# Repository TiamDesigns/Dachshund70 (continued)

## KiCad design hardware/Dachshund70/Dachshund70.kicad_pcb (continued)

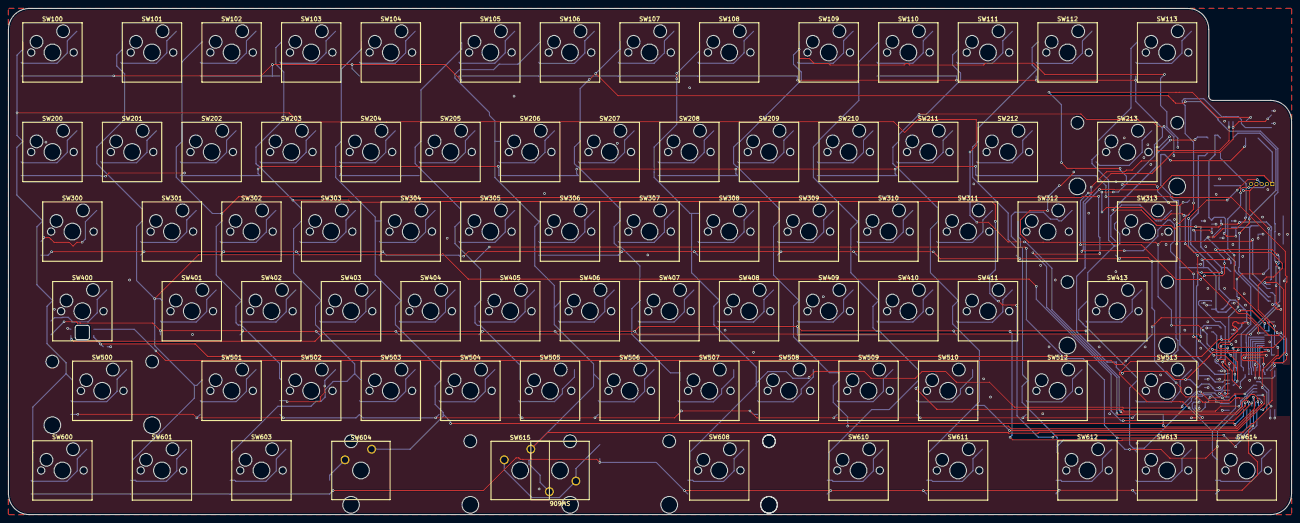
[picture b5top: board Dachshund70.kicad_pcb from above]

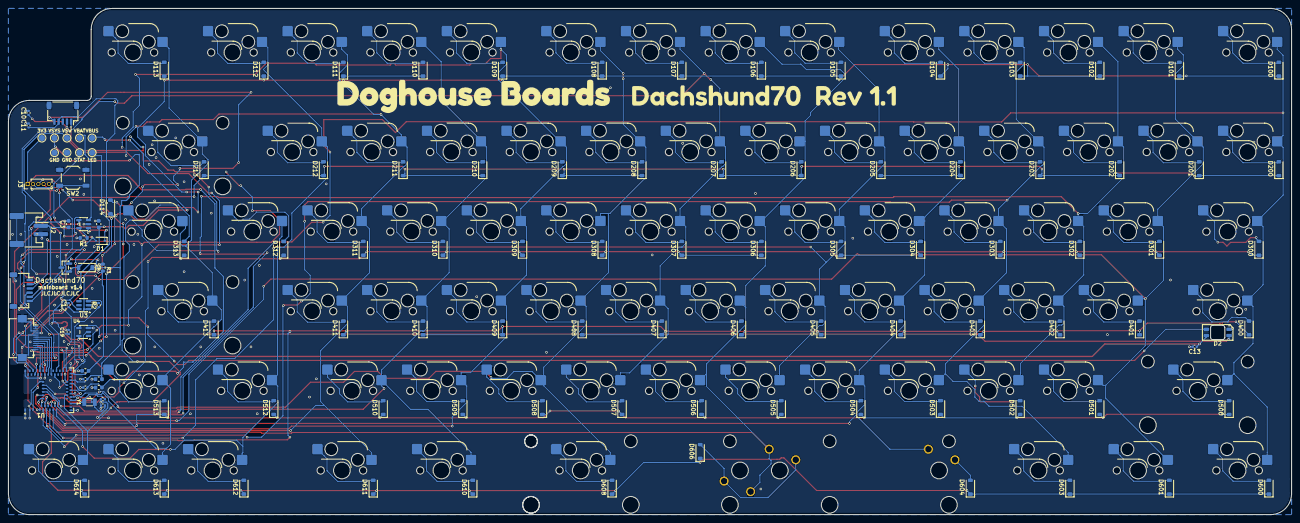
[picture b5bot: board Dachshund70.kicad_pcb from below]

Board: 2 copper layers, 307.0 x 121.1 mm, 207 parts (121 on the bottom side), 130 nets.

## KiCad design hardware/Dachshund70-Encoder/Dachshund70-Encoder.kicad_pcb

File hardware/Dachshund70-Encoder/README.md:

# Dachshund70 encoder module

The roller encoder on its own small board, cabled to the mainboard. Introduced with mainboard Rev 1.1,
which no longer carries the encoder. KiCad 10 project, 2 layers, 1.6 mm FR4.

- **Encoder:** SW1, Bourns PEC12R-2230F-S0024 (shaft parallel to the board, 24 detents, 24 pulses per turn,
  30 mm shaft, push switch pressed along the shaft; no LCSC listing, so source it globally or solder it by hand).
  The 30 mm shaft carries the 2u roller (about 25 mm long, on 19 mm of shaft). Same body and footprint as the
  20 mm PEC12R-2220F-S0024 it replaces (`../3dmodels/Bourns_PEC12R-2x30F-S_standin.step`). Through-hole; its two
  frame tabs are on GND.
- **Cable port:** J1, JST SH 1.0 mm, 5 pins, side entry (SM05B-SRSS-TB), on the **bottom** side, its mouth facing
  +u (toward the shaft). The mainboard's J5 faces it across the notch on the same line, so the cable runs straight
  under the module: about 25 mm overall (housing end to end), 5 parallel wires with both latches on the same side,
  which makes it a reversed cable (J1 pin n to J5 pin 6 − n; the pin numbers below are matched to that). Crimp it
  from SHR-05V-S housings and SSH-003T contacts with 30–32 AWG wire, or shorten a pre-made reversed cable.
  Trim the encoder's through-hole pins to 0.5 mm or less on the bottom: the cable runs right under them (it touches
  the push switch's uncut pins in the model, 0.3 under the A/B/C pins).
- **Nothing else.** The 10 nF debounce capacitors on A and B and the push-switch diode D114 stay on the
  mainboard, so the pin map and the firmware did not change. No expansion ports on either board.

| J5 pin (mainboard) | J1 pin (module) | Net | Encoder pad | MCU pin |
| --- | --- | --- | --- | --- |
| 1 | 5 | COL14 | S1 (push switch) | matrix column 14, with diode D114 on the mainboard |
| 2 | 4 | ENC_A | A | P0.11 |
| 3 | 3 | GND | C (common) | |
| 4 | 2 | ENC_B | B | P0.12 |
| 5 | 1 | ENC_SW | S2 (push switch) | matrix row 0 through D114 |

## Geometry

Module coordinates: u runs along the shaft, toward the hub end of the board (+x of the mainboard's old
encoder); v runs across it (+y); (0, 0) is the board's top-left corner seen from above. Z is measured up
from the PCB's top face.

- Outline 22.5 (u) × 22.0 (v) mm, 1.5 mm corner radius. The right edge is the hub end of the shaft; the wheel
  starts there and the board has nothing under it.
- Encoder pad C at (15.0, 11.0). Body rear face u = 11.5, front face u = 17.5, hub to u = 22.5, shaft tip at
  u = 41.5 (30 mm shaft). Shaft axis at v = 11.0 and 10.0 mm above the PCB top.
- Two mounting holes, 2.2 mm (M2), at (2.7, 2.7) and (2.7, 19.3). The 12.5 mm-wide encoder body spans
  v 4.75 to 17.25.
- J1's pad row at u = 1.3, v = 9 (pin 1) to 13 (pin 5); its body is u 0.8 to 5.8 and its mouth faces +u, so the
  plug sits under the module's left half and the cable leaves toward +u, under the encoder (mainboard x 309.7).
  (Before round 5 it faced -u, into the mainboard's notch edge, where no plug could go in.)
- On the mainboard, J5 is on the back to the right of the corner notch: footprint at (329.8, 49.54) rot 90, pad
  row at x = 331.8 mm, y = 47.54 (pin 5) to 51.54 (pin 1), on the same line as J1 (centre y 49.54, the shaft's
  axis), mouth at x 327.3 facing -x into the notch. The two mouths are 17.6 mm apart; the cable drops 1.8 mm from
  J1 (under the module, z 1.8) to J5 (under the mainboard), and the plate is 7.4 mm above it (6.4 when it floats
  down 1 mm). The notch is open to the mainboard's top edge, x 304.0 to 326.4 mm and y 39.0 to
  57.0 mm, so the module (left edge at x 303.905) sits in it, with a 4.2 mm lobe at (306.6, 57.8) for the
  head of its lower M2 screw (its post is at y 57.82); the upper screw head is inside the notch.

## Status

DRC (kicad-cli, with schematic parity): 0 errors and 0 unconnected items. The only messages are the
library-footprint mismatch on SW1 (the board copy of the footprint is the project's own, like the mainboard's)
and the missing MPN fields that the mainboard also shows. ERC: 0. Not ordered, made or fitted.

LCSC part numbers are blank: the encoder has no LCSC listing (see PROGRESS.md, 2026-10-28), and J1's number
is still to be confirmed, so JLC would source both globally or you solder the encoder by hand.

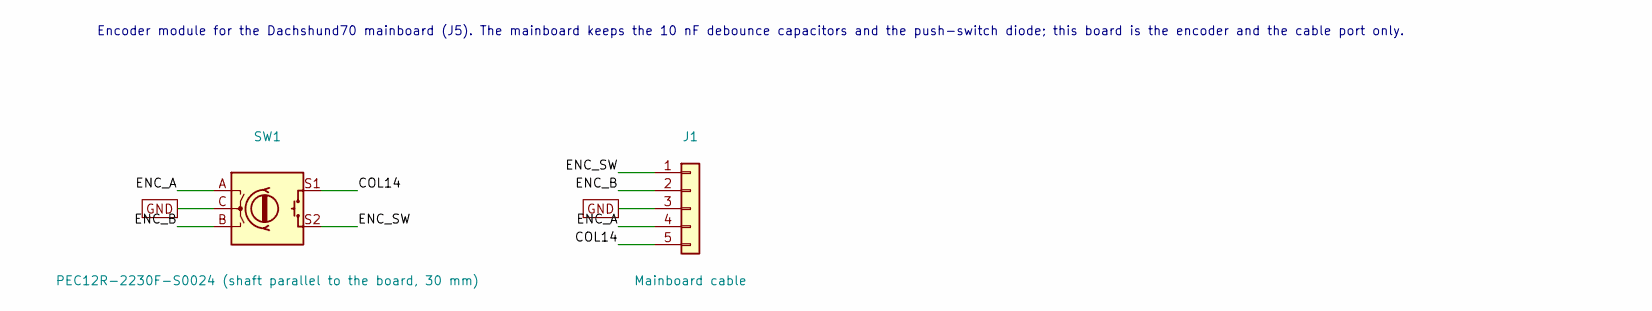
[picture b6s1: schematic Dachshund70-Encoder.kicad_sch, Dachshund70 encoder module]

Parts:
J1: Mainboard cable; JST_SH_SM05B-SRSS-TB_1x05-1MP_P1.00mm_Horizontal; MPN JST SM05B-SRSS-TB
SW1: PEC12R-2230F-S0024 (shaft parallel to the board, 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; RotaryEncoder_Bourns_Horizontal_PEC12R-2x17F-Sxxxx; MPN Bourns PEC12R-2230F-S0024

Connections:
/COL14: J1.5, SW1.S1
/ENC_A: J1.4, SW1.A
/ENC_B: J1.2, SW1.B
/ENC_SW: J1.1, SW1.S2
GND: J1.3, SW1.C

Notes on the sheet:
Encoder module for the Dachshund70 mainboard (J5). The mainboard keeps the 10 nF debounce capacitors and the push-switch diode; this board is the encoder and the cable port only.

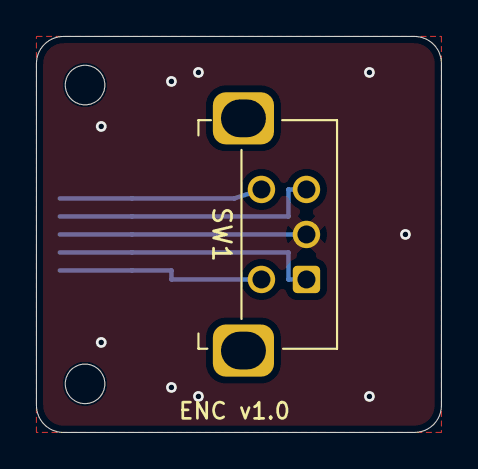
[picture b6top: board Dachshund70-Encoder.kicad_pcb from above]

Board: 2 copper layers, 22.5 x 22.0 mm, 4 parts (1 on the bottom side), 5 nets.

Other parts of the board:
H1, H2: MountingHole_2.2mm_M2

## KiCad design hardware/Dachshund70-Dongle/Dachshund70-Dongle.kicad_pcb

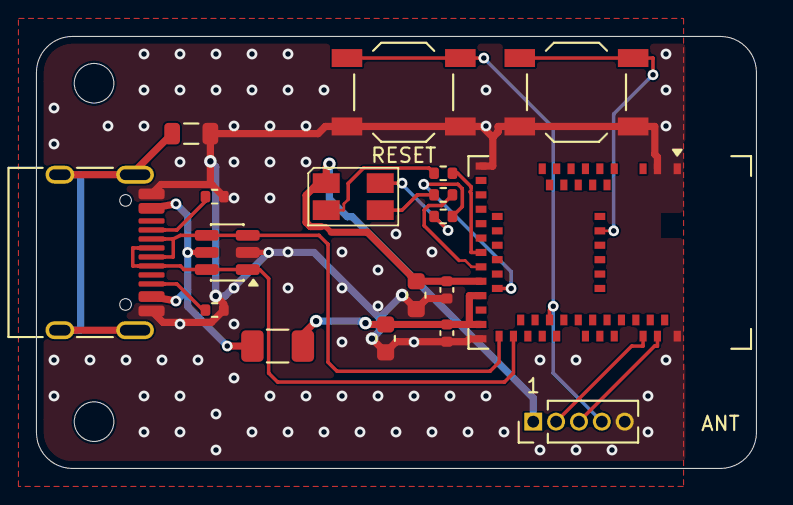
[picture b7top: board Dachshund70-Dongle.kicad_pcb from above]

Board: 2 copper layers, 40.0 x 24.0 mm, 20 parts (0 on the bottom side), 19 nets.

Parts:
C1, C3: 4.7uF; C_0603_1608Metric
C2, C4: 100nF; C_0402_1005Metric
D1: ASMB-MTB0-0A3A2; LED_Avago_PLCC4_3.2x2.8mm_CW
F1: PTC 750mA hold; Fuse_1206_3216Metric
FB1: 600R@100MHz; L_0805_2012Metric
H1, H2: M2; MountingHole_2.2mm_M2
J1: USB-C (HRO TYPE-C-31-M-12); USB_C_Receptacle_HRO_TYPE-C-31-M-12
J2: SWD; PinHeader_1x05_P1.27mm_Vertical
R1, R2: 5.1k; R_0402_1005Metric
R3: 1k; R_0402_1005Metric
R4, R5: 330; R_0402_1005Metric
SW1: Pair; SW_SPST_TL3342
SW2: Reset; SW_SPST_TL3342
U1: USBLC6-2SC6; SOT-23-6
U2: MDBT50Q-P1MV2; Raytac_MDBT50Q

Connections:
/+3V3: C3.1, C4.1, D1.1, J2.1, U2.28
/CC1: J1.A5, R1.1
/CC2: J1.B5, R2.1
/D+: J1.A6, J1.B6, U1.1, U1.6, U2.35
/D-: J1.A7, J1.B7, U1.3, U1.4, U2.34
/LED_B: R5.2, U2.29
/LED_BK: D1.2, R5.1
/LED_G: R4.2, U2.26
/LED_GK: D1.3, R4.1
/LED_R: R3.2, U2.24
/LED_RK: D1.4, R3.1
/NRESET: J2.4, SW2.1, U2.40
/PAIR: SW1.1, U2.57
/SHIELD: FB1.1, J1.SH
/SWDCLK: J2.3, U2.53
/SWDIO: J2.2, U2.51
/VBUS: C1.1, C2.1, F1.2, U2.30, U2.32
/VBUS_RAW: F1.1, J1.A4, J1.A9, J1.B4, J1.B9, U1.5
GND: C1.2, C2.2, C3.2, C4.2, FB1.2, J1.A1, J1.A12, J1.B1, J1.B12, J2.5, R1.2, R2.2, SW1.2, SW2.2, U1.2, U2.1, U2.2, U2.15, U2.33, U2.55

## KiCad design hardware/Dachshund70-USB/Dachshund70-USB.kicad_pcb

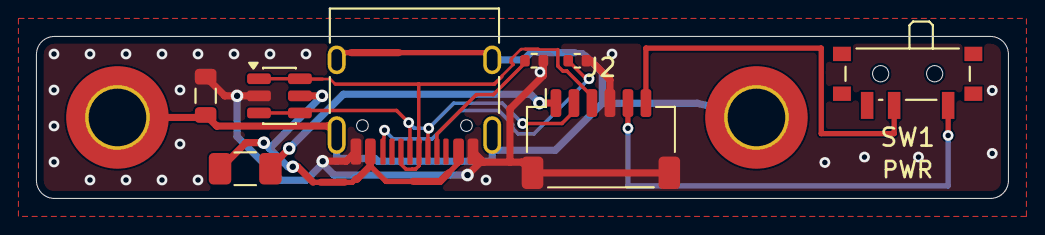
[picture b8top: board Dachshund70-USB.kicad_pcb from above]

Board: 2 copper layers, 54.0 x 9.0 mm, 10 parts (0 on the bottom side), 10 nets.

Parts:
F1: PTC 750mA hold; Fuse_1206_3216Metric
FB1: 600R@100MHz; L_0805_2012Metric
H1, H2: M3; MountingHole_3.2mm_M3_ISO7380_Pad_TopBottom
J1: USB-C (HRO TYPE-C-31-M-12); USB_C_Receptacle_HRO_TYPE-C-31-M-12
J2: Mainboard (JST-SH 6P); JST_SH_SM06B-SRSS-TB_1x06-1MP_P1.00mm_Horizontal
R1, R2: 5.1k; R_0402_1005Metric
SW1: Power; SW_SPDT_PCM12
U1: USBLC6-2SC6; SOT-23-6

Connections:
/CC1: J1.A5, R1.1
/CC2: J1.B5, R2.1
/D+: J1.A6, J1.B6, J2.3, U1.1, U1.6
/D-: J1.A7, J1.B7, J2.2, U1.3, U1.4
/SHIELD: FB1.1, H1.1, H2.1, J1.SH
/VBAT: J2.5, SW1.1
/VBAT_SW: J2.6, SW1.2
/VBUS: F1.2, J2.1
/VBUS_RAW: F1.1, J1.A4, J1.A9, J1.B4, J1.B9, U1.5
GND: FB1.2, J1.A1, J1.A12, J1.B1, J1.B12, J2.4, J2.MP, R1.2, R2.2, U1.2

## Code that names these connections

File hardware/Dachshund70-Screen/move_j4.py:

"""One-off edit of the mainboard: J4, the hand-wired 2.54 mm display header, becomes an
8-pin 0.5 mm FFC socket for the screen board (Hirose FH12-8S, top side, under the plate notch) and the
eight display nets are rerouted to it. Kept for the record; run it once, in KiCad 10's Python, from the
repo root. The schematic side is done separately (J4's symbol becomes Conn_01x08_MountingPin, MP to GND).

J4's pins sit at the same x and y as the screen board's J2 (the FFC loops round between them), so pin n
here meets J2 pin 9 - n. Pin 1 (3V3) is at the back (smaller y), pin 8 (BUSY) at the front. The
socket sits under the plate's screen notch, 2.7 mm behind the SWD header J3 so its body clears J3.
"""
import pcbnew

PCB = "hardware/Dachshund70/Dachshund70.kicad_pcb"
FP_DIR = "/usr/share/kicad/footprints/Connector_FFC-FPC.pretty"
FP_NAME = "Hirose_FH12-8S-0.5SH_1x08-1MP_P0.50mm_Horizontal"
XY = (327.9, 94.9)           # pads y 93.15-96.65, clear of J3 (the SWD header, from y 100.4)
M, F = pcbnew.ToMM, pcbnew.FromMM

b = pcbnew.LoadBoard(PCB)
nets = {n: b.FindNet(n) for n in ("+3V3", "GND", "/DISP_DIN", "/DISP_CLK", "/DISP_CS", "/DISP_DC", "/DISP_RST",
                                  "/DISP_BUSY")}
DISP = [n for n in nets if n.startswith("/DISP")]


TRACKS = list(b.GetTracks())    # looked up once: pcbnew's track list can't be re-read after a Remove
REMOVE = []


def P(x, y):
    return pcbnew.VECTOR2I(F(x), F(y))


def near(a, xy, tol=0.002):
    return abs(M(a.x) - xy[0]) < tol and abs(M(a.y) - xy[1]) < tol


def find_track(net, layer, a, c):
    for t in TRACKS:
        if t in REMOVE:
            continue
        if t.GetClass() == "PCB_VIA" or t.GetNetname() != net or t.GetLayerName() != layer:
            continue
        if (near(t.GetStart(), a) and near(t.GetEnd(), c)) or (near(t.GetStart(), c) and near(t.GetEnd(), a)):
            return t
    raise SystemExit("no track %s %s %r %r" % (net, layer, a, c))


def find_via(net, xy):
    for t in TRACKS:
        if t.GetClass() == "PCB_VIA" and t.GetNetname() == net and near(t.GetPosition(), xy, 0.01):
            return t
    raise SystemExit("no via %s %r" % (net, xy))


def drop_track(net, layer, a, c):
    REMOVE.append(find_track(net, layer, a, c))


def move_end(net, layer, a, c, old, new):
    """Move the end of track a-c that sits at old to new."""
    t = find_track(net, layer, a, c)
    if near(t.GetStart(), old):
        t.SetStart(P(*new))
    else:
        t.SetEnd(P(*new))


def track(net, layer, pts, w):
    for (ax, ay), (cx, cy) in zip(pts, pts[1:]):
        t = pcbnew.PCB_TRACK(b)
        t.SetStart(P(ax, ay))
        t.SetEnd(P(cx, cy))
        t.SetWidth(F(w))
        t.SetLayer(pcbnew.F_Cu if layer == "F" else pcbnew.B_Cu)
        t.SetNet(nets[net])
        b.Add(t)


def via(net, x, y):
    v = pcbnew.PCB_VIA(b)
    v.SetPosition(P(x, y))
    v.SetWidth(F(0.6))
    v.SetDrill(F(0.3))
    v.SetNet(nets[net])
    b.Add(v)


# ---- the old header and every F.Cu stub to it
old = b.FindFootprintByReference("J4")
path = old.GetPath()
for t in TRACKS:
    if t.GetClass() != "PCB_VIA" and t.GetLayerName() == "F.Cu" and t.GetNetname() in DISP:
        if M(t.GetStart().y) > 104.0 or M(t.GetEnd().y) > 104.0:      # the display runs below y 104 only
            REMOVE.append(t)
for n, xy in (("/DISP_DIN", (304.126, 111.2844)), ("/DISP_CLK", (303.4476, 109.2921)),
              ("/DISP_CS", (302.8174, 107.3224)), ("/DISP_BUSY", (302.2158, 105.4471))):
    REMOVE.append(find_via(n, xy))
for gx, gy in ((323.85, 95.25), (321.150933, 109.600499), (302.0277, 108.961626)):   # GND stitching in the way
    REMOVE.append(find_via("GND", (gx, gy)))
b.Remove(old)

# 3V3 used to pass through the header's pin 1 on its way to J3 (F.Cu in, B.Cu out): a via there now

# B.Cu ends of the four F.Cu runs: the vias move so the runs come out DIN on top, BUSY at the bottom
drop_track("/DISP_DIN", "B.Cu", (304.126, 111.2844), (304.3172, 111.0932))
move_end("/DISP_DIN", "B.Cu", (304.3172, 111.0932), (304.3172, 80.2828), (304.3172, 111.0932), (304.3172, 105.81))
track("/DISP_DIN", "B", [(304.3172, 105.81), (304.126, 106.0)], 0.25)          # clear of ROW4 at x 304.77
move_end("/DISP_CLK", "B.Cu", (303.4476, 109.2921), (303.4476, 88.3391), (303.4476, 109.2921), (303.4476, 106.5))
track("/DISP_CLK", "B", [(303.4476, 106.5), (303.5476, 106.8)], 0.25)
drop_track("/DISP_CS", "B.Cu", (302.8636, 107.2762), (302.8174, 107.3224))
move_end("/DISP_CS", "B.Cu", (302.8636, 88.3939), (302.8636, 107.2762), (302.8636, 107.2762), (302.8636, 107.58))
move_end("/DISP_BUSY", "B.Cu", (302.2158, 105.4471), (302.2158, 88.3849), (302.2158, 105.4471), (302.2158, 109.4))
# DC: its B.Cu run from the north now stops at a via at y 108.2
drop_track("/DISP_DC", "B.Cu", (321.81, 112.5), (323.8355, 110.4745))
move_end("/DISP_DC", "B.Cu", (323.8355, 110.4745), (323.8355, 100.5464), (323.8355, 110.4745), (323.8355, 108.2))
# RST: its B.Cu run now stops at a via at y 108.8 instead of looping south of the old header
for a, c in (((324.35, 112.5), (322.0256, 114.8244)), ((322.0256, 114.8244), (309.2719, 114.8244)),
             ((309.2719, 114.8244), (307.9155, 113.468)), ((307.9155, 113.468), (307.9155, 113.1497)),
             ((307.9155, 113.1497), (307.9155, 112.8313)), ((307.9155, 112.8313), (307.9155, 109.0255)),
             ((307.9155, 109.0255), (309.5086, 107.4324))):
    drop_track("/DISP_RST", "B.Cu", a, c)
track("/DISP_RST", "B", [(309.5086, 107.4324), (309.5086, 108.8)], 0.25)
for n, x, y in (("+3V3", 309.11, 112.5), ("/DISP_DIN", 304.126, 106.0), ("/DISP_CLK", 303.5476, 106.8), ("/DISP_CS", 302.8636, 107.58),
                ("/DISP_BUSY", 302.2158, 109.4), ("/DISP_DC", 323.8355, 108.2), ("/DISP_RST", 309.5086, 108.8)):
    via(n, x, y)

for t in REMOVE:
    b.Remove(t)

# ---- the new socket
fp = pcbnew.FootprintLoad(FP_DIR, FP_NAME)
fp.SetFPIDAsString("Connector_FFC-FPC:" + FP_NAME)
fp.SetReference("J4")
fp.SetValue("Screen board")
fp.GetField(pcbnew.FIELD_T_DATASHEET).SetText(
    "https://www.hirose.com/product/document?clcode=CL0580-1255-6-55&productname=FH12-8S-0.5SH(55)&series=FH12"
    "&documenttype=Catalog&lang=en&documentid=D31690_en")
fp.GetField(pcbnew.FIELD_T_DESCRIPTION).SetText(
    "Screen board cable port: 8-pin 0.5 mm FFC, same-side contacts "
    "(pin 1 3V3, 2 GND, 3 DIN, 4 CLK, 5 CS, 6 DC, 7 RST, 8 BUSY)")
for fname, fval in (("MPN", "Hirose FH12-8S-0.5SH(55)"), ("LCSC", "")):
    fld = pcbnew.PCB_FIELD(fp, fp.GetNextFieldOrdinal(), fname)
    fld.SetText(fval)
    fld.SetVisible(False)
    fld.SetLayer(pcbnew.F_Fab)
    fp.Add(fld)
fp.SetPath(path)
fp.SetPosition(P(*XY))
b.Add(fp)
for r in (90, 270):          # pads on the +x side, so the mouth faces -x
    fp.SetOrientationDegrees(r)
    p1 = [p for p in fp.Pads() if p.GetNumber() == "1"][0]
    if M(p1.GetPosition().x) > XY[0]:
        break
PIN = {"1": "+3V3", "2": "GND", "3": "/DISP_DIN", "4": "/DISP_CLK", "5": "/DISP_CS", "6": "/DISP_DC",
       "7": "/DISP_RST", "8": "/DISP_BUSY", "MP": "GND"}
for p in fp.Pads():
    p.SetNet(nets[PIN[p.GetNumber()]])
    if p.GetNumber() != "MP":
        print("pad", p.GetNumber(), M(p.GetPosition().x), M(p.GetPosition().y))
fp.Reference().SetPosition(P(XY[0] - 1.6, XY[1]))
fp.Reference().SetTextAngleDegrees(90)

# ---- routes. Rows under the socket body; 3V3, DIN, CLK and CS go down between J3 and the front mounting
# pad, DC, RST and BUSY right of it, then jog left under the pad; all run west under J3.
PX = 329.75                  # pad centres
W = 0.18
track("+3V3", "F", [(323.0, 106.0), (323.85, 106.0), (323.85, 93.15), (PX, 93.15)], 0.25)
track("/DISP_DIN", "F", [(PX, 94.15), (324.29, 94.15), (324.29, 106.8), (304.926, 106.8), (304.126, 106.0)], W)
track("/DISP_CLK", "F", [(PX, 94.65), (324.68, 94.65), (324.68, 107.19), (303.9376, 107.19), (303.5476, 106.8)], W)
track("/DISP_CS", "F", [(PX, 95.15), (325.07, 95.15), (325.07, 107.58), (302.8636, 107.58)], W)
track("/DISP_DC", "F", [(PX, 95.65), (327.95, 95.65), (327.95, 99.85), (325.6, 102.2), (325.6, 108.2),
                        (323.8355, 108.2)], W)
track("/DISP_RST", "F", [(PX, 96.15), (328.55, 96.15), (328.55, 99.85), (326.2, 102.2), (326.2, 108.8),
                         (309.5086, 108.8)], W)
# GND: the front mounting pad sits in a pocket of the pour, and pin 2 between two tracks; a via each
track("GND", "F", [(326.5, 98.55), (325.8, 97.3)], 0.3)
track("GND", "F", [(PX, 93.65), (331.0, 93.65)], 0.2)
via("GND", 325.8, 97.3)
via("GND", 331.0, 93.65)
track("/DISP_BUSY", "F", [(PX, 96.65), (PX, 97.1), (329.15, 97.7), (329.15, 99.85), (326.8, 102.2), (326.8, 109.4),
                          (302.2158, 109.4)], W)

b.BuildConnectivity()
pcbnew.ZONE_FILLER(b).Fill(b.Zones())
b.Save(PCB)
print("saved")

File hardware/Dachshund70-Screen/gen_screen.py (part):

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# U1 (TPS61222, fixed 5 V) boosts the mainboard's 3V3; FB goes straight to VOUT, as the datasheet says for the
# fixed versions. The panel draws tens of microamps, so U1's 5.5 uA quiescent current is most of the cost.
# U1's EN comes from J4-8 (the e-paper overlays' BUSY), pulled up by R1, so the 5 V is on unless the firmware
# drives that pin low. EXTMODE is tied high: VCOM is inverted by the EXTCOMIN pulse, not over SPI.
# C3, C4 and C5 are the capacitors Sharp asks for (VDD >= 1 uF, VDDA >= 0.1 uF, DISP 0.1 uF), close to J1.

# Panel FPC pin -> net (Sharp LS027B7DH01 specification, "Input/output terminals")
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MAINBOARD = os.path.join(HERE, "..", "Dachshund70", "Dachshund70.kicad_pcb")
POWER = ("+3V3", "+5V", "GND")

# J1's pads run the other way from the panel's pins: the tail folds back under the glass, so (looking down on
# the board) panel pin 1 lands at the top, where J1's pad 10 is. J1 pin n = panel pin 11 - n (see README).
SOCKET = {n: PANEL[11 - n] for n in range(1, 11)}

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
